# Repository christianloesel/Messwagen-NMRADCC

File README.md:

# Messwagen-NMRADCC
Messwagen basierend auf ATmega328P

[zum Wiki](https://github.com/ghostriderace/Messwagen-NMRADCC/wiki)

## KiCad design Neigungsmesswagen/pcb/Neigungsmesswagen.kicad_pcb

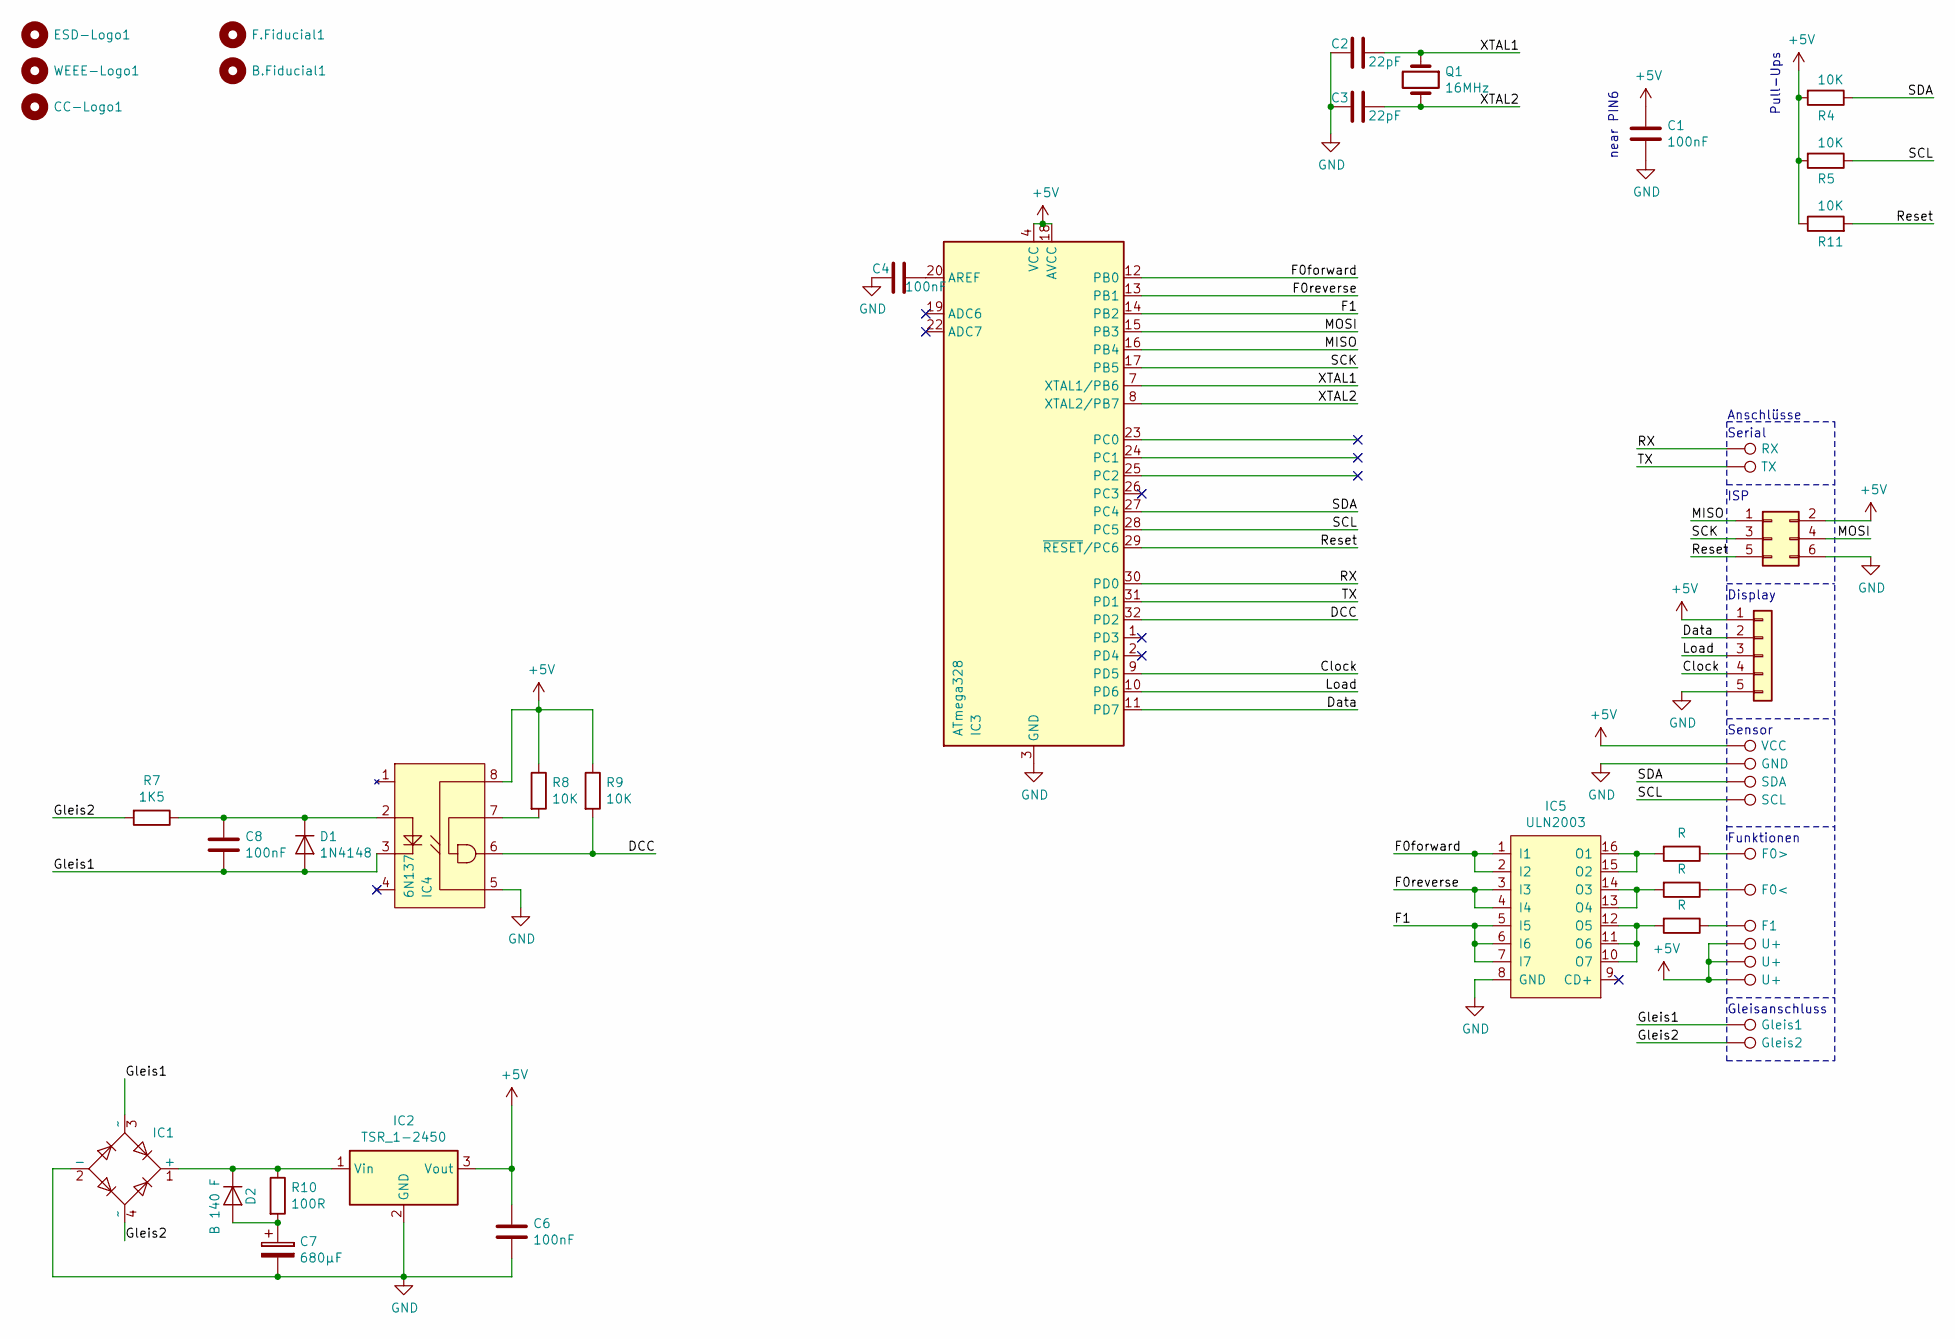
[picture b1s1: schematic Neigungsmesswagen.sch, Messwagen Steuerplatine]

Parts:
B.Fiducial1: ---; Fiducial_1mm_Dia_2.54mm_Outer_CopperBottom
C1, C4, C6, C8: 100nF; C_0805_2012Metric_Pad1.15x1.40mm_HandSolder
C2, C3: 22pF; C_0805_2012Metric_Pad1.15x1.40mm_HandSolder
C7: 680µF; C_Elec_10x10.2
CC-Logo1: ---; CC-BY-NC-SA_10x3.6mm_SilkScreen
D1: 1N4148; D_MiniMELF_Handsoldering
D2: B 140 F; D_SMA_Handsoldering
ESD-Logo1: ---; ESD-Logo_6.6x6mm_SilkScreen
F.Fiducial1: ---; Fiducial_1mm_Dia_2.54mm_Outer_CopperTop
IC1: D_Bridge; Diode_Bridge_Vishay_DFS
IC2: TSR_1-2450; Converter_DCDC_TRACO_TSR-1_THT
IC3: ATmega328; TQFP-32_7x7mm_P0.8mm
IC4: 6N137; DIP-8_W7.62mm_Socket_LongPads
IC5: ULN2003; SOIC-16_3.9x9.9mm_P1.27mm
J1: ISP; PinHeader_2x03_P2.54mm_Vertical
J2: Display; PinHeader_1x05_P2.54mm_Vertical_SMD
Q1: 16MHz; Crystal_SMD_HC49-SD
R1, R2, R3: R; R_0805_2012Metric_Pad1.15x1.40mm_HandSolder
R4, R5, R8, R9, R11: 10K; R_0805_2012Metric_Pad1.15x1.40mm_HandSolder
R7: 1K5; R_0805_2012Metric_Pad1.15x1.40mm_HandSolder
R10: 100R; R_0805_2012Metric_Pad1.15x1.40mm_HandSolder
TP1: RX; TestPoint_Pad_2.0x2.0mm
TP2: TX; TestPoint_Pad_2.0x2.0mm
TP4: F0>; TestPoint_Pad_2.0x2.0mm
TP5: F0<; TestPoint_Pad_2.0x2.0mm
TP6: F1; TestPoint_Pad_2.0x2.0mm
TP7: SDA; TestPoint_Pad_2.0x2.0mm
TP8: SCL; TestPoint_Pad_2.0x2.0mm
TP9, TP10, TP11: U+; TestPoint_Pad_2.0x2.0mm
TP12: VCC; TestPoint_Pad_2.0x2.0mm
TP13: GND; TestPoint_Pad_2.0x2.0mm
TP15: Gleis1; TestPoint_Pad_2.0x2.0mm
TP16: Gleis2; TestPoint_Pad_2.0x2.0mm
WEEE-Logo1: ---; WEEE-Logo_4.2x6mm_SilkScreen

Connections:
+5V: C1.1, C6.1, IC2.3 (Vout), IC3.4 (VCC), IC3.6 (VCC), IC3.18 (AVCC), IC4.8 (VCC), J1.2, J2.1, R4.2, R5.2, R8.1, R9.1, R11.1, TP9.1, TP10.1, TP11.1, TP12.1
/Clock: IC3.9 (PD5), J2.4
/DCC: IC3.32 (PD2), IC4.6 (VO), R9.2
/Data: IC3.11 (PD7), J2.2
/F0forward: IC3.12 (PB0), IC5.1 (I1), IC5.2 (I2)
/F0reverse: IC3.13 (PB1), IC5.3 (I3), IC5.4 (I4)
/F1: IC3.14 (PB2), IC5.5 (I5), IC5.6 (I6), IC5.7 (I7)
/Gleis1: C8.2, D1.2 (A), IC1.3 (~~), IC4.3 (Cathode), TP15.1
/Gleis2: IC1.4 (~~), R7.2, TP16.1
/Load: IC3.10 (PD6), J2.3
/MISO: IC3.16 (PB4), J1.1
/MOSI: IC3.15 (PB3), J1.4
/RX: IC3.30 (PD0), TP1.1
/Reset: IC3.29 (~RESET~/PC6), J1.5, R11.2
/SCK: IC3.17 (PB5), J1.3
/SCL: IC3.28 (PC5), R5.1, TP8.1
/SDA: IC3.27 (PC4), R4.1, TP7.1
/TX: IC3.31 (PD1), TP2.1
/XTAL1: C2.1, IC3.7 (XTAL1/PB6), Q1.1
/XTAL2: C3.1, IC3.8 (XTAL2/PB7), Q1.2
GND: C1.2, C2.2, C3.2, C4.2, C6.2, C7.2, IC1.2 (-), IC2.2 (GND), IC3.3 (GND), IC3.5 (GND), IC3.21 (GND), IC4.5 (GND), IC5.8 (GND), J1.6, J2.5, TP13.1
unnamed: C4.1, IC3.20 (AREF)
unnamed: C7.1, D2.2 (A), R10.2
unnamed: C8.1, D1.1 (K), IC4.2 (Anode), R7.1
unnamed: D2.1 (K), IC1.1 (+), IC2.1 (Vin), R10.1
unnamed: IC4.7 (VE), R8.2
unnamed: IC5.10 (O7), IC5.11 (O6), IC5.12 (O5), R3.2
unnamed: IC5.13 (O4), IC5.14 (O3), R2.2
unnamed: IC5.15 (O2), IC5.16 (O1), R1.2
unnamed: R1.1, TP4.1
unnamed: R2.1, TP5.1
unnamed: R3.1, TP6.1

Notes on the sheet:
Sensor
Funktionen
Anschlüsse
Gleisanschluss
Display
ISP
near PIN6
Pull-Ups
Serial

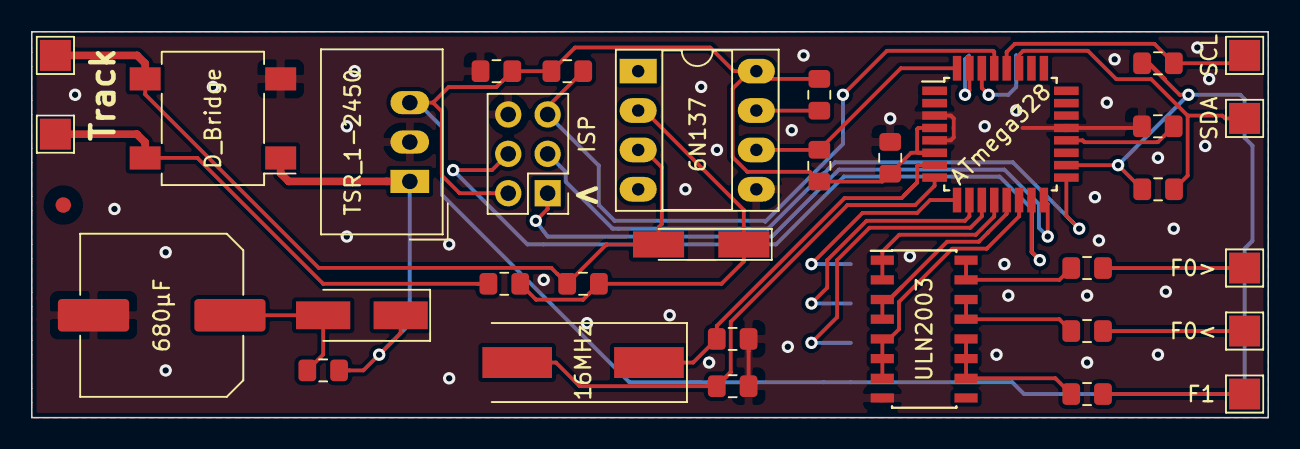
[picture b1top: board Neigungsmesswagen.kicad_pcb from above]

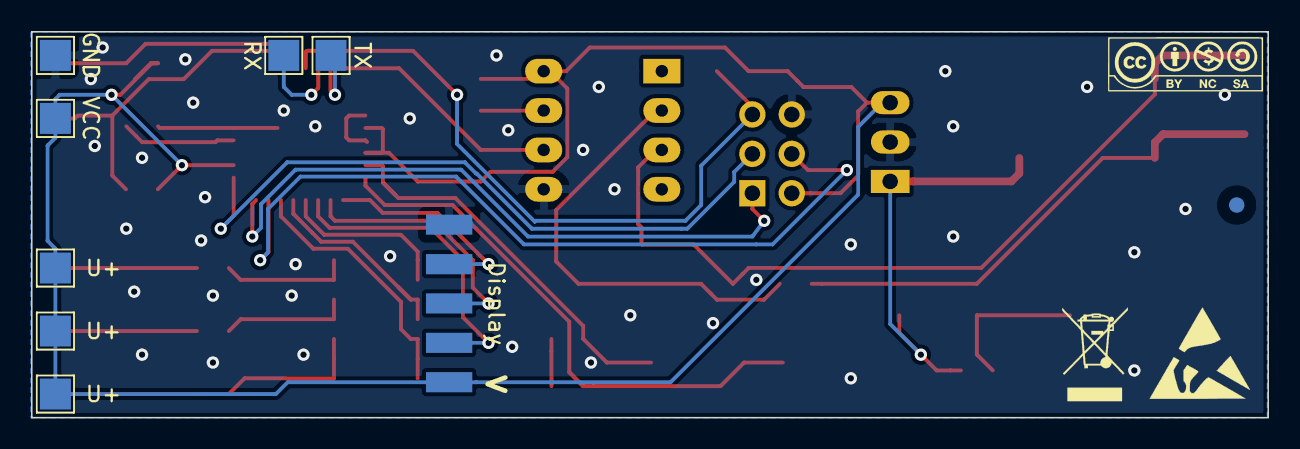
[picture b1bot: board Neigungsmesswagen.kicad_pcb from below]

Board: 2 copper layers, 79.8 x 24.9 mm, 46 parts (11 on the bottom side), 32 nets.

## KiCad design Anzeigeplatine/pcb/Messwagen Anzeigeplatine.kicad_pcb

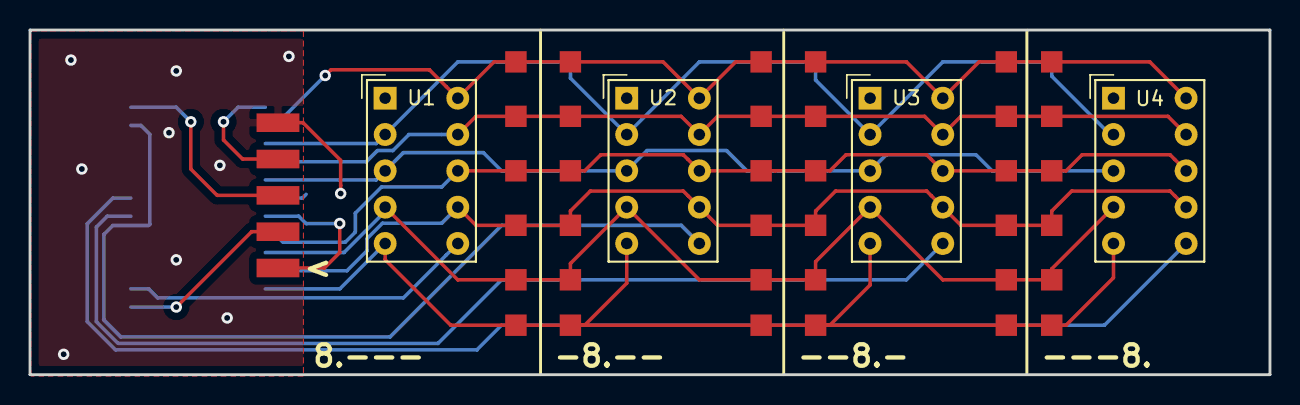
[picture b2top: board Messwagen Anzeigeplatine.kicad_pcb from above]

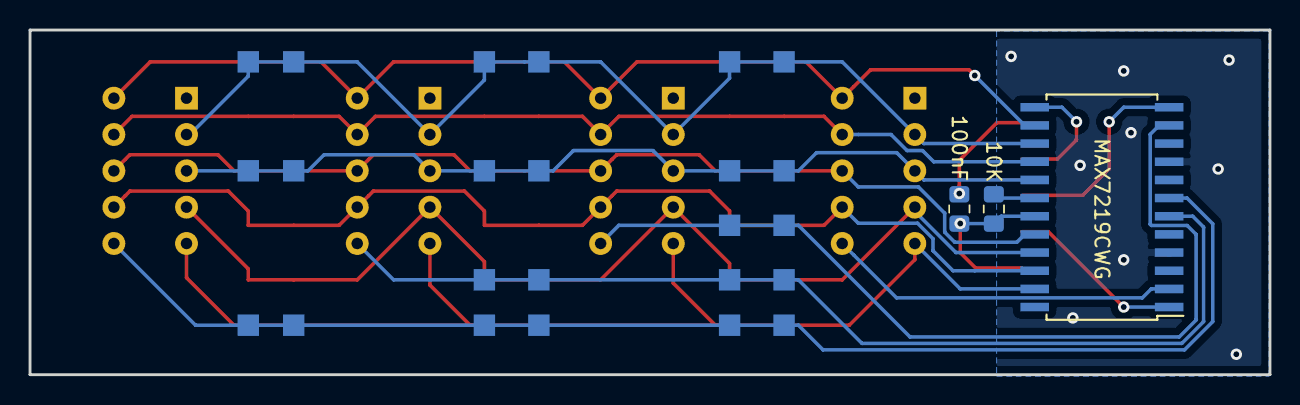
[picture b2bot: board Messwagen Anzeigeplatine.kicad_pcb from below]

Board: 2 copper layers, 86.7 x 24.1 mm, 68 parts (27 on the bottom side), 18 nets.

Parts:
C1: 100nF; C_0805_2012Metric_Pad1.15x1.40mm_HandSolder
IC1: MAX7219CWG; SOIC-24W_7.5x15.4mm_P1.27mm
J1: Conn_01x05; PinHeader_1x05_P2.54mm_Vertical_SMD
R1: 10K; R_0805_2012Metric_Pad1.15x1.40mm_HandSolder
TP1, TP2, TP3, TP4, TP5, TP6, TP7, TP8, TP9, TP10, TP11, TP12, TP13, TP14, TP15, TP16, TP17, TP18, TP19, TP20, TP21, TP22, TP23, TP24, TP25, TP26, TP27, TP28, TP29, TP30, TP31, TP32, TP33, TP34, TP35, TP36, TP37, TP38, TP39, TP40, TP41, TP42, TP43, TP44, TP45, TP46, TP47, TP48, TP49, TP50, TP51, TP52, TP53, TP54, TP55, TP56, TP57, TP58, TP59, TP60: TestPoint; Lötpad
U1, U2, U3, U4: HDSP-7503; HDSP-A151

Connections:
+5V: C1.1, IC1.19, J1.1, R1.2
/CLK: IC1.13, J1.4
/DP: IC1.22, TP8.1, TP19.1, TP30.1, TP40.1, TP50.1, TP59.1, U1.7, U2.7, U3.7, U4.7
/D_IN: IC1.1, J1.2
/LOAD: IC1.12, J1.3
/PA: IC1.14, TP1.1, TP12.1, TP23.1, TP33.1, TP43.1, TP52.1, U1.10, U2.10, U3.10, U4.10
/PB: IC1.16, TP2.1, TP13.1, TP24.1, TP34.1, TP44.1, TP53.1, U1.9, U2.9, U3.9, U4.9
/PC: IC1.20, TP3.1, TP14.1, TP25.1, TP35.1, TP45.1, TP54.1, U1.8, U2.8, U3.8, U4.8
/PD: IC1.23, TP4.1, TP15.1, TP26.1, TP36.1, TP46.1, TP55.1, U1.5, U2.5, U3.5, U4.5
/PE: IC1.21, TP5.1, TP16.1, TP27.1, TP37.1, TP47.1, TP56.1, U1.4, U2.4, U3.4, U4.4
/PF: IC1.15, TP6.1, TP17.1, TP28.1, TP38.1, TP48.1, TP57.1, U1.2, U2.2, U3.2, U4.2
/PG: IC1.17, TP7.1, TP18.1, TP29.1, TP39.1, TP49.1, TP58.1, U1.3, U2.3, U3.3, U4.3
/T1: IC1.2, U1.6
/T2: IC1.11, TP9.1, TP20.1, U2.6
/T3: IC1.6, TP10.1, TP21.1, TP31.1, TP41.1, U3.6
/T4: IC1.7, TP11.1, TP22.1, TP32.1, TP42.1, TP51.1, TP60.1, U4.6
GND: C1.2, IC1.4, IC1.9, J1.5
unnamed: IC1.18, R1.1

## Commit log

2020-03-11 Create fp-lib-table
